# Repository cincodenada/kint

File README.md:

The kinT keyboard controller is a replacement for your Kinesis Advantage or
Advantage 2 ergonomic keyboards.

You can use it for example…

* to build or modify your own keyboard
* to [work around bugs in the standard controller](https://michael.stapelberg.ch/posts/2013-03-21-kinesis_custom_controller/)
* because you prefer to run open source software such as the [QMK firmware](https://docs.qmk.fm/), even on your keyboard

See also:

* [My blog post introducing the kinT keyboard controller](https://michael.stapelberg.ch/posts/2020-07-09-kint-kinesis-keyboard-controller/)
* [My twitch stream recording introducing the kinT keyboard controller](https://youtu.be/I0kwQbnhlfk)

## Quick overview

<table border="0" width="100%">
<tr>
<td width="33%">

3D render (front, LEDs)
</td>
<td width="33%">

3D render (back, components)
</td>
<td width="33%">

schematic
</td>
</tr>
</table>

## Building your own kinT keyboard controller

1. Follow [“Buying the board and components (Bill of
   materials)”](https://github.com/kinx-project/kint#buying-the-board-and-components-bill-of-materials). When
   ordering from OSH Park (board) and Digi-Key (components), you’ll get the
   minimum quantity of 3 boards for 72 USD (24 USD per board), and one set of
   components for 49 USD.

   * If you have any special requirements regarding which Teensy microcontroller
     to use, this is the step where you would replace the Teensy 3.6 with your
     choice.

1. Wait for the components to arrive. When ordering from big shops like Digi-Key
   or Mouser, this typically takes 2 days to many places in the world.

1. Wait for the boards to arrive. This takes 6 days in the best case when
   ordering from OSH Park with their Super Swift Service option. In general, the
   longer you are willing to wait, the cheaper it is going to get.

1. Follow [the soldering
   guide](https://github.com/kinx-project/kint#soldering). This will take about
   an hour.

1. [Install the firmware](https://github.com/kinx-project/kint#installing-the-firmware)

## Why use the kinT instead of the older replacement board?

* The kinT supports both, the older Kinesis Advantage (KB500) **and** the newer
  Kinesis Advantage 2 (KB600) keyboards. They differ in how the thumb pads are
  connected. See the soldering instructions below.

   * NOTE: If this is the *only* feature you’re interested in, and you already
     have a custom keyboard controller for your older Kinesis, [check out the
     u6w5 adapter
     board](https://github.com/kinx-project/adapter-use-kb600-with-kb500-controller)
     I made!

* The kinT is made for the newer Teensy 3.x and 4.x series, which will remain
  widely available for years to come, whereas the [Teensy++ 2.0 is
  discontinued](https://www.pjrc.com/store/teensypp.html).

* The kinT is a smaller PCB (4.25 x 3.39 inches, or 108.0 x 86.1 mm), which makes it:

   * more compact: can be inserted/removed without having to unscrew a key well.

   * cheaper: 72 USD for 3 boards at oshpark, instead of 81 USD.

* The kinT silkscreen
  ([front](https://raw.githubusercontent.com/kinx-project/kint/44e6c8be96a0e1e13ada5eafdeba8c51a2d6c9e8/pcb-3d-render-front-v2020-06-23.png),
  [back](https://raw.githubusercontent.com/kinx-project/kint/44e6c8be96a0e1e13ada5eafdeba8c51a2d6c9e8/pcb-3d-render-back-v2020-06-23.png))
  and
  [schematic](https://github.com/kinx-project/kint/blob/44e6c8be96a0e1e13ada5eafdeba8c51a2d6c9e8/schematic-v2020-06-23.pdf)
  are much much clearer, making assembly a breeze.

* The kinT is a good starting point for your own project:

   * kinT was designed in the open source [KiCad](https://kicad.org/)
     program, meaning you do not need any license subscriptions.

   * The clear silkscreen and schematic make development and debugging easier.

* On the kinT, the Teensy no longer has to be soldered onto the board upside down.

* On the kinT, the FPC connectors have been moved for less strain on the cables.

* The kinT makes possible lower-cost builds: if you don’t need the scroll lock,
  num lock and keypad LEDs, you can use a Teensy LC for merely 11 USD.

## Compatibility: which Teensy to use?

The kinT keyboard controller was made for the Teensy 3.x and 4.x series of
devices, which are ARM based.

The older Atmel based Teensy++ 2.0 are also supported, but they require cutting
one set of solder jumpers and closing a second set, to account for clashing pin
assignments.

Which Teensy should you buy for your build? Here are a few considerations:

* I have been using the Teensy 4.1 for many months without problems.

* I used the Teensy 3.6 for multiple years, and many others are happy with it,
  too.

* The Teensy++ 2.0 used to be the most popular choice, in part because it was
  the only option with the the predecessor keyboard controller. The [Teensy++
  2.0 is discontinued](https://www.pjrc.com/store/teensypp.html), so I would no
  longer recommend it for new keyboard builds.

* If you are an advanced user of the QMK firmware, note that despite QMK working
  on the Teensy 3.6, [some features are not yet
  ported/working](https://github.com/kinx-project/kint/issues/10). As QMK was
  originally made for AVR micro controllers, you will likely find best overall
  QMK feature availability with the older Teensy++ 2.0.

### Reference: full Teensy compatibility chart

TODO: add power consumption as a column. relevant for using the keyboard with a laptop on the go

| teensy         | LEDs | Cost   | input latency | clock speed | MCU         | QMK                                                                   |
|----------------|------|--------|---------------|-------------|-------------|-----------------------------------------------------------------------|
| teensy++ 2.0   | yes  | $24.00 | 3.27ms        | 16 MHz AVR  | AT90USB1286 | 0.13.17 or newer                                                      |
| ~~teensy 3.0~~ | no   |        |               | 48 MHz M4   | MK20DX128   | untested                                                              |
| ~~teensy 3.1~~ | no   |        |               |             | MK20DX256   | untested                                                              |
| teensy LC      | no   | $11.65 | ?             | 48 MHz M0+  |             | [untested](https://github.com/kinx-project/kint/issues/1)             |
| teensy 3.2     | no   | $19.80 | ?             | 72 MHz M4   |             | unlikely ([interest?](https://github.com/kinx-project/kint/issues/2)) |
| teensy 3.5     | yes  | $24.25 | ?             | 120 MHz M4F | MK64FX      | unlikely ([interest?](https://github.com/kinx-project/kint/issues/3)) |
| teensy 3.6     | yes  | $29.25 | 1.97ms        | 180 MHz M4F | MK66FX      | 0.14.0 or newer                                                       |
| teensy 4.0     | no   | $19.95 | 0.9ms         | 600 MHz M7  | MIMXRT1062  | 0.14.0 or newer                                                       |
| teensy 4.1     | yes  | $26.85 | 0.9ms         | 600 MHz M7  | MIMXRT1062  | 0.14.0 or newer                                                       |

See [this blog post for more details on keyboard input
latency](https://michael.stapelberg.ch/posts/2021-05-08-keyboard-input-latency-qmk-kinesis/).

## Buying the board and components (Bill of materials)

To buy the board, you can:

* [order the kinT controller from OSH Park](https://oshpark.com/shared_projects/YSZAuKc0) starting at 72 USD
* [order the kinT controller from Aisler](https://aisler.net/p/JQIIIJSL) starting at 18 EUR
* [order the kinT controller from JLCPCB](https://github.com/kinx-project/kint/tree/master/gerbers/jlcpcb)
* or upload the [kint.kicad_pcb
  file](https://github.com/kinx-project/kint/blob/master/kicad/kint.kicad_pcb)
  to the manufacturing service you prefer.

To buy the components, check out the [kinT BOM in the Octopart BOM
tool](https://octopart.com/bom-tool/4AnOAR3f), from where you can conveniently
buy all components via Digi-Key or Mouser.

For your convenience, this is the full BOM (links go to Octopart):

| Part Number                                                                               | Count | Cost   | Description               | Note                                               |
|-------------------------------------------------------------------------------------------|-------|--------|---------------------------|----------------------------------------------------|
| [Teensy 3.6](https://octopart.com/dev-14057-sparkfun-76356774?r=sp)                       | 1     | $32.5  |                           | [your choice!](#compatibility-which-teensy-to-use) |
| [Würth 61301011121](https://octopart.com/61301011121-w%C3%BCrth+elektronik-18818159?r=sp) | 8     | $0.89  | 10 position 2.54mm header | 6 for Teensy<br>2 for KB500<br>0 for KB600         |
| [Molex 39-53-2135](https://octopart.com/39-53-2135-molex-7670149?r=sp)                    | 6     | $1.24  | 13 position FPC connector | 4 for KB500<br>6 for KB600                         |
| [Kingbright APT3216QBC/D](https://octopart.com/apt3216qbc%2Fd-kingbright-5355642?r=sp)    | 4     | $0.47  | 1206 SMD LED              | blue 470nm<br>chose your color!                    |
| [Vishay CRCW120610K0FKEAC](https://octopart.com/crcw120610k0fkeac-vishay-20811529)        | 4     | $0.10  | 1206 10K resistor         | value determines LED brightness                    |
|                                                                                           |       | $48.45 |                           |                                                    |

Note: with all parts (except for the Molex 39-53-2135 FPC connector), there is
no need to get the specific versions from the BOM above — if you have LEDs,
resistors and pin headers still lying around from other projects, feel free to
re-use them!

## Soldering

All the soldering connections on the kinT keyboard controller are easy to make,
so the whole assembly can be done at home, with a cheap soldering iron and basic
electronic hobby equipment. A build takes about 1 hour of time and involves a
little over 100 soldering connections.

For example, I used the [Miniware TS100 soldering
iron](https://hackaday.com/2017/07/24/review-ts100-soldering-iron/), which can
be found for 50-60 EUR or USD.

If you’re new to soldering, check out [this excellent soldering reference card
from adafruit](https://twitter.com/zekjur/status/952596267884056576).

You can also [watch me solder a kinT keyboard controller on live
stream](https://youtu.be/I0kwQbnhlfk?t=5880) (from 1:38:00 to 3:33:53). The
process can be done in under an hour if you’re not talking to a live audience at
the same time :-). I want to add an edited and higher-quality video, too.

### Soldering instructions for the Teensy 3.x or 4.x

1. Populate the FPC connectors J2, J3, J4, J7 (all keyboards) and J1, J8 for the
   newer Advantage 2 (KB600). Turn the board around and solder all their pins.

1. Solder resistors R1, R2, R3, R4 and the four LEDs onto the board.

   * LEDs are directional parts! Their marker marks the cathode, which is
     labeled as C on the kinT. For details about the marker, refer to the LED
     datasheet, e.g. the [Kingbright APT3216QBC/D data
     sheet](https://www.kingbrightusa.com/images/catalog/SPEC/APT3216QBC-D.pdf)
     if you are using the LED from the [Bill of Materials
     (BOM)](#buying-the-board-and-components-bill-of-materials).

   * If you’re new to SMD (Surface Mount Devices) soldering, check out [How to
     Hand Solder SMD](http://www.davidhaillant.com/smd-soldering/), which
     explains what I call the “One pad at a time” method.

1. Turn the board around and place (but don’t solder) **3 rows of pin headers**
   (top, bottom, vertical) in the Teensy holes.

   * The vertical pin header is required for powering the LEDs.

   * If you want your Teensy to be removable, you can use socket headers here
     instead. [See the instructions below](#using-socket-headers).

1. Place your Teensy on top of the pin header and solder all its pins.

1. Turn the board around and solder all the pin header pins.

1. For the older Advantage (KB500) keyboard, populate pin headers J5, J6 and
   solder their pins.

### Soldering instructions for the Teensy++ 2.0

Follow the [instructions for the Teensy 3.x or 4.x
above](#soldering-instructions-for-the-teensy-3x-or-4x), and then:

1. Using a small knife such as a hobby knife, cut the traces between the pads
   of jumpers JP4, JP5, and JP6. This will disconnect pin 7, pin 15 and pin 16.

   * If you haven't cut traces like this before, SparkFun has a [brief
     illustrated tutorial][jumper-tut] about working with jumpers that is a
     good reference.

2. Close the solder jumpers JP1, JP2, JP3. These will remap pin 7, pin 15 and
   pin 16 onto pins that can be used with the Teensy++ 2.0.

If you are [using socket headers](#using-socket-headers) so that the Teensy is
removable, you can later upgrade to a Teensy 3.x or 4.x by desoldering JP1,
JP2, and JP3, and reclosing the jumpers JP4, JP5, and JP6.

[jumper-tut]: https://learn.sparkfun.com/tutorials/how-to-work-with-jumper-pads-and-pcb-traces/what-is-a-jumper

### Using socket headers

Due to the space for the USB cable in the back, there's not enough room in the
case for a standard socket header, but there are low-profile pin headers that
do fit. [These square-pin socket headers](short-sockets) and [pins](short-pins)
with 0.180" (4.57mm) insulation height have been verified to fit in the KB500,
and will probably fit the KB600 as well. Round "Swiss-style" headers may also
work, but make sure to get the appropriate matching pins for whatever socket
you order.

To build with socket headers, follow the [standard instructions
above](#soldering-instructions-for-the-teensy-3x-or-4x), but instead of the
steps involving soldering the pin headers, do the following:

1. Turn the board around and solder **3 rows of socket headers** (top, bottom,
   vertical) in the Teensy holes on the kinT board.

1. Place and solder the corresponding **3 rows of pin headers** (top, bottom,
   vertical) on the Teensy itself.

1. Insert the Teensy into the sockets.

[short-sockets]: https://octopart.com/search?q=SLW-124-01-T-S&currency=USD&specs=0
[short-pins]: https://octopart.com/search?q=TSW-124-23-G-S&currency=USD&specs=0

## Installing the firmware

You can use the QMK Configurator online build tool to compile the QMK firmware for
your kinT keyboard controller, or customize your layout.

Alternatively, you can install the pre-built, tested firmware file (default QMK
keymap and settings) we offer, for example to test whether issues are related to
your self-compiled firmware.

| Teensy           | QMK Configurator                                                             | pre-built, tested firmware                                                                                                                |
|------------------|------------------------------------------------------------------------------|-------------------------------------------------------------------------------------------------------------------------------------------|
| Teensy++ 2.0     | [QMK Configurator (kint2pp)](https://config.qmk.fm/#/kinesis/kint2pp/LAYOUT) | [kinesis_kint2pp_default.hex](https://github.com/kinx-project/kint/blob/master/default-firmware/kinesis_kint2pp_default.hex) (2020-07-09) |
| Teensy 3.6       | [QMK Configurator (kint36)](https://config.qmk.fm/#/kinesis/kint36/LAYOUT)   | [kinesis_kint36_default.hex](https://github.com/kinx-project/kint/blob/master/default-firmware/kinesis_kint36_default.hex) (2020-07-09)   |
| Teensy 4.0 / 4.1 | [QMK Configurator (kint41)](https://config.qmk.fm/#/kinesis/kint41/LAYOUT)   | TODO                                                                                                                                      |

You can install these .hex files with the [Teensy
Loader](https://www.pjrc.com/teensy/loader.html).

To compile your own firmware, see [QMK: Get
Started](https://docs.qmk.fm/#/?id=get-started) and refer to the [full Teensy
compatibility chart](#reference-full-teensy-compatibility-chart) above to find
the QMK branch to work with.

## Debugging / Troubleshooting

### General technique: highlight connections in KiCad

1. Install [KiCad](https://kicad.org/) (free and open source)
1. Clone https://github.com/kinx-project/kint/ and open `kicad/kint.pro` in KiCad
1. Select `Tools` → `Edit PCB`
1. Select `View` → `Flip Board View`, because the front side of kinT contains the LEDs, the back side contains the connectors.
1. Select `Highlight Net`, the second icon from the top in the right icon bar
1. Click on the pin of interest. In the bottom left, you’ll see the Net Name (e.g. `COL_3`), and KiCad will highlight all connected traces.

### Issue: LEDs not working

See also [Example issue #13](https://github.com/kinx-project/kint/issues/13) for
a full debugging walk-through.

* Check the orientation of your LEDs, as they are directional parts.

   * The marker printed on the kinT board marks the LED cathode, which is
     labeled as C on the kinT. For details about the marker, refer to the LED
     datasheet, e.g. the [Kingbright APT3216QBC/D data
     sheet](https://www.kingbrightusa.com/images/catalog/SPEC/APT3216QBC-D.pdf)
     if you are using the LED from the [Bill of Materials
     (BOM)](#buying-the-board-and-components-bill-of-materials).

* If your Teensy is not soldered yet (or removed from its socket), you can test your LEDs with a multimeter:
   * switch your multimeter to diode test mode
   * place the black probe (`COM`) on e.g. Teensy pin 12 (`LED_CAPS_LOCK`)
   * place the red probe on the anode (A) of your LED
   * the LED should light up now, or it might be defective:

* Measure that the LED pins behave as expected, e.g. Teensy pin 12 for `LED_CAPS_LOCK`:
   * you should measure 3.3V when the LED is turned off
   * you should measure 0V when the LED is turned on

* Check that you soldered in the vertical pin header, which supplies 3.3V to the LEDs:

### Issue: Keys not working

See also [Example issue #16](https://github.com/kinx-project/kint/issues/16) for
a full debugging walk-through.

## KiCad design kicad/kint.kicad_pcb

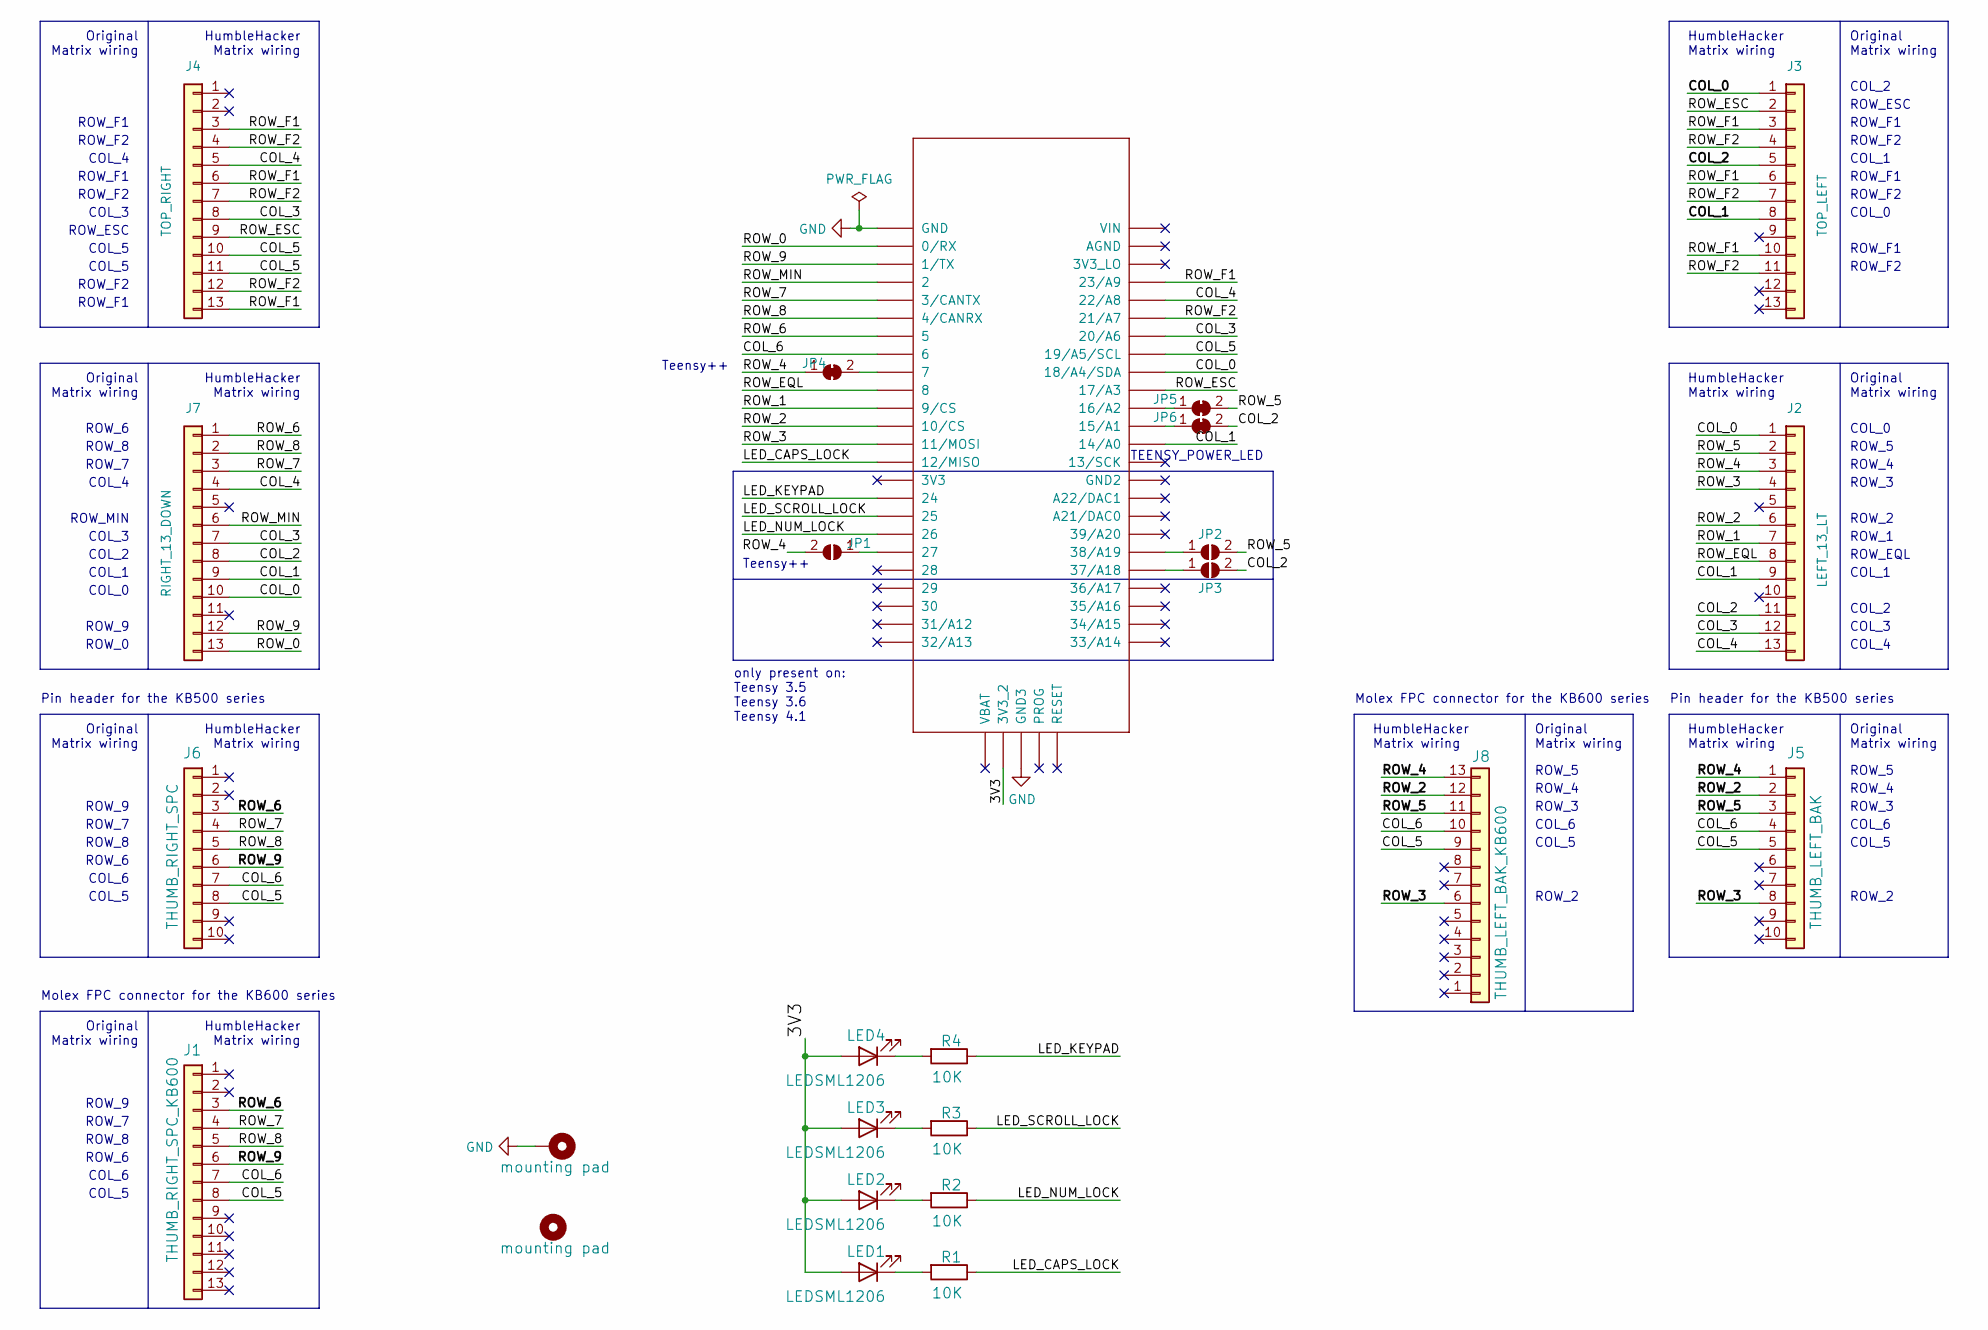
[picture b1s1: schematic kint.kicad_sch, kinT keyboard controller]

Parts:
H1: mounting pad; MountingHole_4.3mm_M4_Pad
H2: mounting pad; MountingHole_6mm
J1: THUMB_RIGHT_SPC_KB600; 39-53-2135; MPN 39-53-2135; digikeypn WM14526-ND
J2: LEFT_13_LT; 39-53-2135; MPN 39-53-2135; digikeypn WM14526-ND
J3: TOP_LEFT; 39-53-2135; MPN 39-53-2135; digikeypn WM14526-ND
J4: TOP_RIGHT; 39-53-2135; MPN 39-53-2135; digikeypn WM14526-ND
J5: THUMB_LEFT_BAK; PinHeader_1x10_P2.54mm_Vertical; MPN 39-53-2135; digikeypn WM14526-ND
J6: THUMB_RIGHT_SPC; PinHeader_1x10_P2.54mm_Vertical; MPN 39-53-2135; digikeypn WM14526-ND
J7: RIGHT_13_DOWN; 39-53-2135; MPN 39-53-2135; digikeypn WM14526-ND
J8: THUMB_LEFT_BAK_KB600; 39-53-2135; MPN 39-53-2135; digikeypn WM14526-ND
JP1, JP2, JP3: SolderJumper_2_Open; SolderJumper-2_P1.3mm_Open_TrianglePad1.0x1.5mm
JP4, JP5, JP6: SolderJumper_2_Bridged; SolderJumper-2_P1.3mm_Bridged2Bar_RoundedPad1.0x1.5mm
LED1, LED2, LED3, LED4: LEDSML1206; LED_1206_3216Metric_Pad1.42x1.75mm_HandSolder; MPN APT3216QBC/D; digikeypn 754-1439-1-ND
R1, R2, R3, R4: 10K; R_1206_3216Metric_Pad1.42x1.75mm_HandSolder; MPN CRCW120610K0FKEAC; digikeypn 541-3983-1-ND
U1: TEENSY_3.5_3.6

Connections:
/3V3: LED1.2 (A), LED2.2 (A), LED3.2 (A), LED4.2 (A), U1.3V3_2
/COL_0: J2.1, J3.1, J7.10, U1.18/A4/SDA
/COL_1: J2.9, J3.8, J7.9, U1.14/A0
/COL_2: J2.11, J3.5, J7.8, JP3.2 (B), JP6.2 (B)
/COL_3: J2.12, J4.8, J7.7, U1.20/A6
/COL_4: J2.13, J4.5, J7.4, U1.22/A8
/COL_5: J1.8, J4.10, J4.11, J5.5, J6.8, J8.9, U1.19/A5/SCL
/COL_6: J1.7, J5.4, J6.7, J8.10, U1.6
/LED_CAPS_LOCK: R1.1, U1.12/MISO
/LED_KEYPAD: R4.1, U1.24
/LED_NUM_LOCK: R2.1, U1.26
/LED_SCROLL_LOCK: R3.1, U1.25
/ROW_0: J7.13, U1.0/RX
/ROW_1: J2.7, U1.9/CS
/ROW_2: J2.6, J5.2, J8.12, U1.10/CS
/ROW_3: J2.4, J5.8, J8.6, U1.11/MOSI
/ROW_4: J2.3, J5.1, J8.13, JP1.2 (B), JP4.1 (A)
/ROW_5: J2.2, J5.3, J8.11, JP2.2 (B), JP5.2 (B)
/ROW_6: J1.3, J6.3, J7.1, U1.5
/ROW_7: J1.4, J6.4, J7.3, U1.3/CANTX
/ROW_8: J1.5, J6.5, J7.2, U1.4/CANRX
/ROW_9: J1.6, J6.6, J7.12, U1.1/TX
/ROW_EQL: J2.8, U1.8
/ROW_ESC: J3.2, J4.9, U1.17/A3
/ROW_F1: J3.3, J3.6, J3.10, J4.3, J4.6, J4.13, U1.23/A9
/ROW_F2: J3.4, J3.7, J3.11, J4.4, J4.7, J4.12, U1.21/A7
/ROW_MIN: J7.6, U1.2
GND: H1.1, U1.GND, U1.GND3
unnamed: JP1.1 (A), U1.27
unnamed: JP2.1 (A), U1.38/A19
unnamed: JP3.1 (A), U1.37/A18
unnamed: JP5.1 (A), U1.16/A2
unnamed: JP6.1 (A), U1.15/A1
unnamed: LED1.1 (K), R1.2
unnamed: LED2.1 (K), R2.2
unnamed: LED3.1 (K), R3.2
unnamed: LED4.1 (K), R4.2
unnamed: JP4.2 (B), U1.7

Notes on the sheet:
COL_6
TEENSY_POWER_LED
ROW_F2
ROW_6
Pin header for the KB500 series
Molex FPC connector for the KB600 series
ROW_7
COL_3
ROW_4
ROW_ESC
COL_0
ROW_3
ROW_2
ROW_1
Original Matrix wiring
ROW_5
ROW_MIN
Teensy++
ROW_F1
HumbleHacker Matrix wiring
ROW_EQL
ROW_9
COL_4
COL_5
COL_1
COL_2
only present on: Teensy 3.5 Teensy 3.6 Teensy 4.1
ROW_8
ROW_0

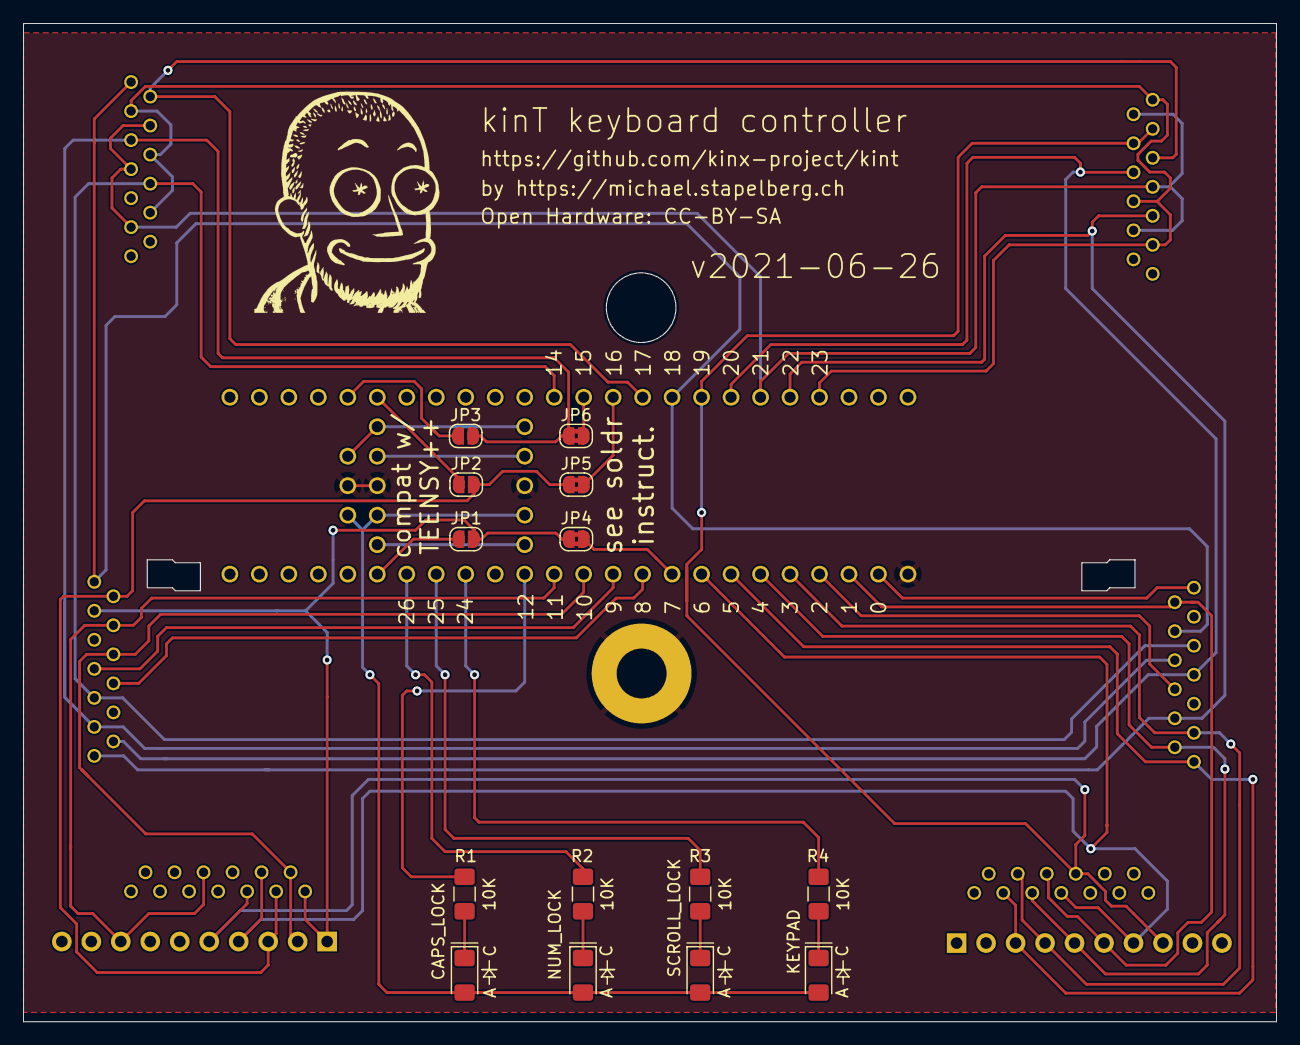
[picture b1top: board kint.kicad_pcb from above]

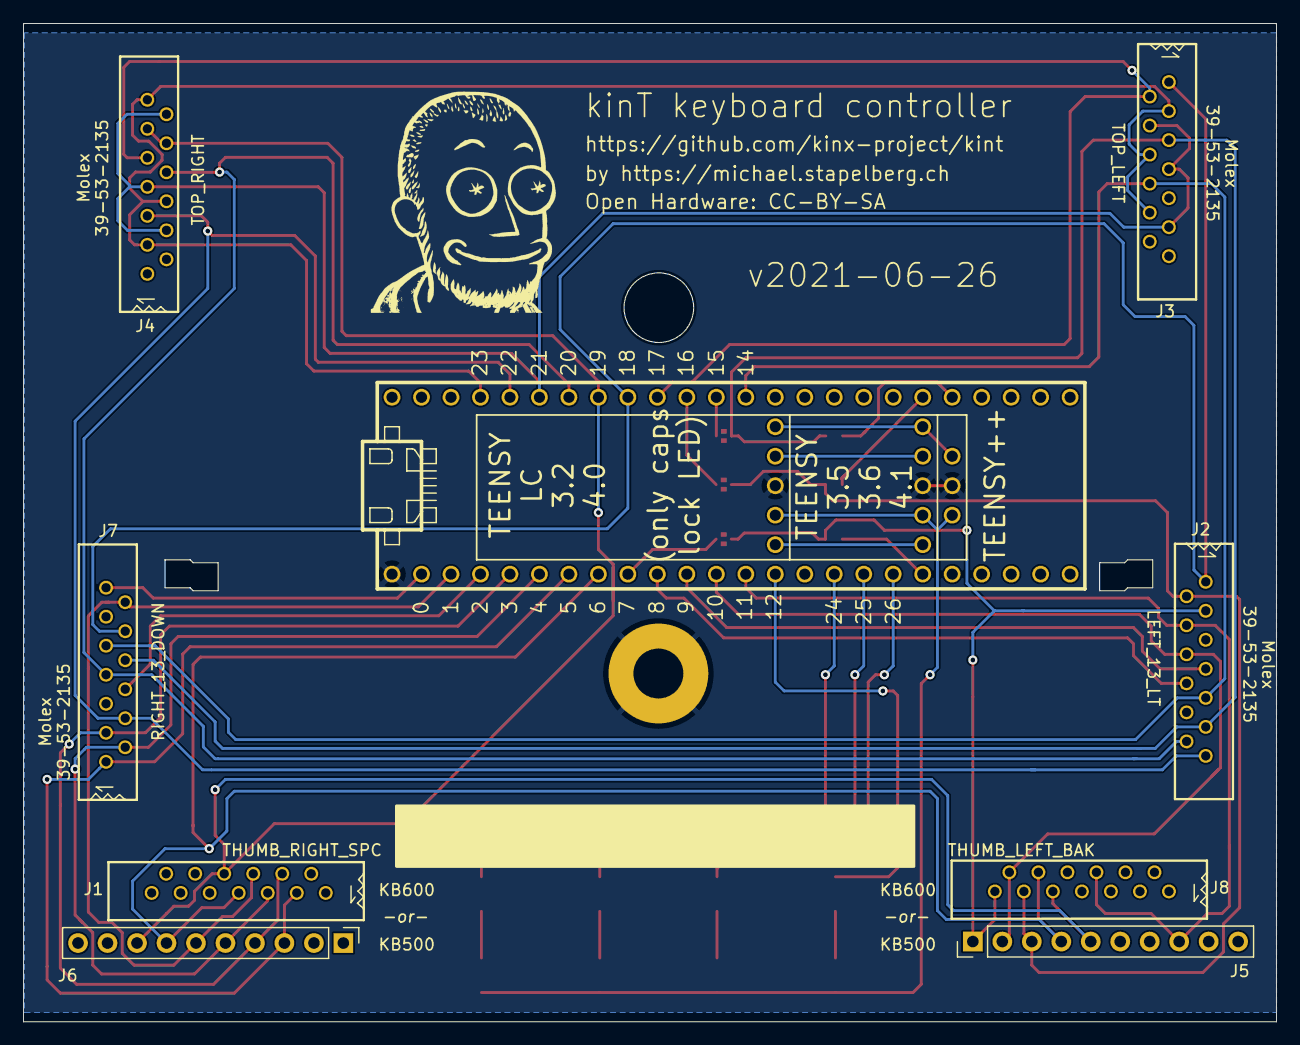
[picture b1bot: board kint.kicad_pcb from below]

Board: 2 copper layers, 107.9 x 86.0 mm, 25 parts (9 on the bottom side), 38 nets.

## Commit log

2021-04-27 Add more jumpers for Teensy++ 2.0 compat
    This avoids requiring folks to pull pins out of headers for Teensy++ 2.0
    compatibility, instead just requiring them to cut the traces, which I
    think is better and more importantly is reversible, so that if someone
    builds with a Teensy++ 2.0 and then wants to replace it with a 3.6, they
    can just re-close the new jumpers, desolder the old ones, and be good to
    go.
2021-04-27 Update README to reflect new jumpers
2022-01-30 Fix up board and schematic in KiCad
    Not too bad, I think the merging was worth it
2022-01-30 Update README for headers and per feedback
    Remove references to removing pins, jumpers all the way
2022-01-30 Re-fill zones
    Forgot to do this after the latest tweaks
2022-01-31 Fix extra "that"
2022-01-31 should -> may, I haven't actually tried the Swiss headers

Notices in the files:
README.md:
License: CC BY-SA 4.0
kicad/kint.kicad_pcb:
Open Hardware: CC-BY-SA
